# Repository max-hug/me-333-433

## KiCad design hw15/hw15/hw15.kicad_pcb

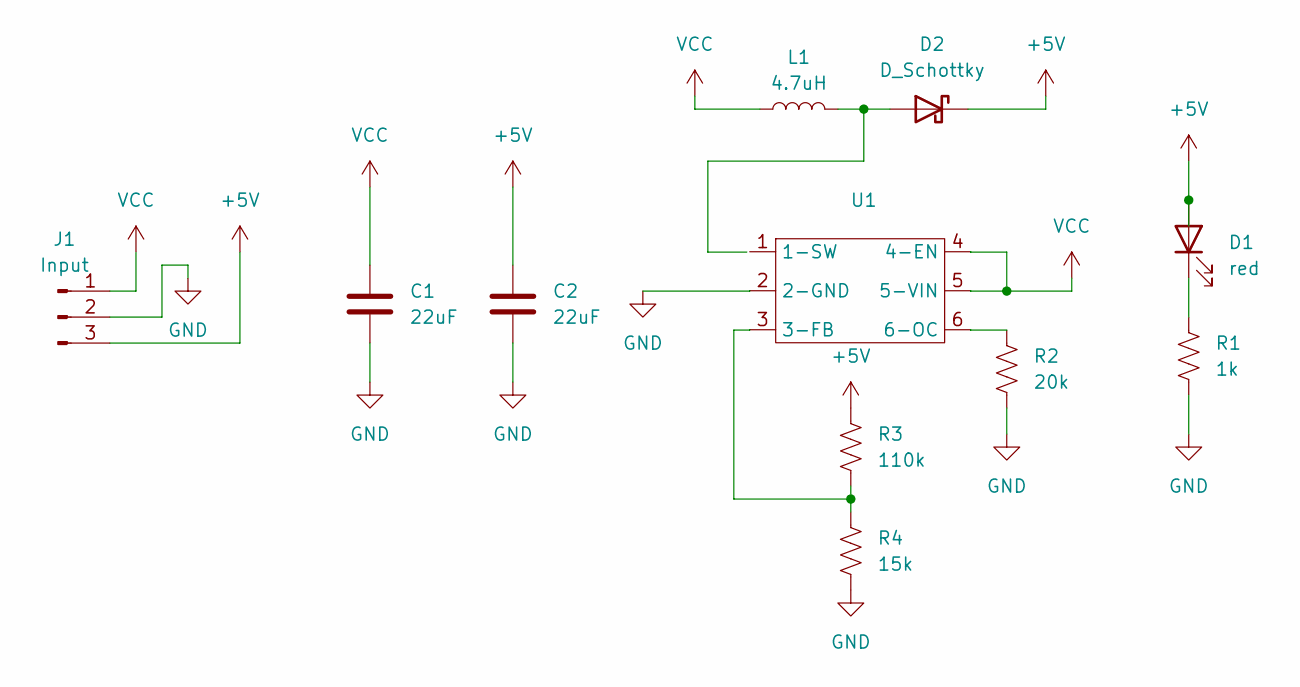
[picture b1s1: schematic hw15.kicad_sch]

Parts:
C1, C2: 22uF; C_1210_3225Metric
D1: red; LED_1206_3216Metric
D2: D_Schottky; D_SOD-123
J1: Input; PinHeader_1x03_P2.54mm_Vertical
L1: 4.7uH; L_0805_2012Metric
R1: 1k; R_0603_1608Metric
R2: 20k; R_0603_1608Metric
R3: 110k; R_0603_1608Metric
R4: 15k; R_0603_1608Metric
U1: TSOT-23-6_HandSoldering

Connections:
+5V: C2.1, D1.2 (A), D2.1 (K), J1.3, R3.1
GND: C1.2, C2.2, J1.2, R1.2, R2.2, R4.2, U1.2 (2-GND)
unnamed: D1.1 (K), R1.1
unnamed: D2.2 (A), L1.2
unnamed: R3.2, R4.1, U1.3 (3-FB)
unnamed: R2.1, U1.6 (6-OC)
VCC: C1.1, J1.1, L1.1, U1.4 (4-EN), U1.5 (5-VIN)

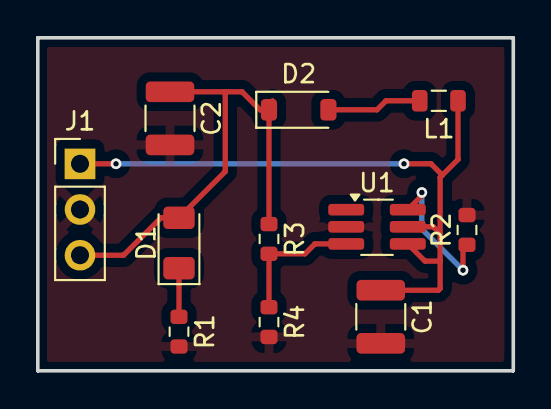
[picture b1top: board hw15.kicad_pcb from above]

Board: 2 copper layers, 26.4 x 18.5 mm, 11 parts (0 on the bottom side), 7 nets.

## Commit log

2025-01-07 test
2025-01-09 hw 2
2025-01-11 fixed ascii
2025-01-13 hw2 submit
2025-02-17 feedback
2025-02-24 feedback completed
2025-04-03 random final project nonsesnee
2025-04-03 reorganizing
2025-04-08 hw1+2
2025-04-08 reorganized
2025-05-05 hw10
2025-05-11 hw11
2025-05-22 lots
2025-05-25 hw16
2025-06-03 hw12+17
